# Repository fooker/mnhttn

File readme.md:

# mnhTTn

mnhTTn is a 36 key column-staggered split keyboard using Cherry MX ULP switches.
Designed to be as flat and lightweight as possible.

## Features
* [Cherry MX ULP Switches](https://www.cherry.de/mx-ulp-click)
* Bluetooth [via SEEED XIAO BLE](https://www.seeedstudio.com/Seeed-XIAO-BLE-nRF52840-p-5201.html)
* Only 7.2mm height

## Layout

## PCB
[Here](/board/) you can find the KiCad fies for the PCB.

To archive minimal height, you can order the PCB as low as 0.6mm thick.
But this requires additional attention while soldering on the swithches to prevent the board from warping caused by thermal expansion.

## Keycaps
There are no keycaps available off the shelve but have been manifactured using MJF in nylon.
The models are availabe [here](/keycaps/).

## Case
The (slightly overengineered) 3d printed case is available [here](/case/).
The case is best printed in PETG and you need the following material to build it:
- 2 round magnets with a diameter of 5mm and a height of 3mm
- 7 machines screws with a flat and countersunk head of size 2x10mm
- A festival/concert/entrance wristband of you'r favorite band or message
- A few drops of superglue

## Build Guide
The build guide can be found [here](/docs/buildguide.md).

## Firmware
My [ZMK config](https://github.com/fooker/mnhttn-zmk) for the mnhTTn.

## Photos
\
\
\
\

## Other Versions
There are other versions, derivats and spin-offs of this keyboard:
- **[mnhTTn48](https://github.com/venc0r/mnhttn)**: A 5*4+3+1 Keys versions with an additional top row and and extra key right above the diode array

If you have build or want to build something based on the mnhTTn keyboard or know about somebody that has created something with it, feel free to reach out and I will happly extend this list and provide support.

## Credits and inspirationt
The idea to creat such a keyboard emerged from the wonderfull [Click! Clack! Hack!](https://www.clickclackhack.de/) community.

The layout of the board is inspired by [TOTEM](https://github.com/GEIGEIGEIST/TOTEM).

And I got a lot of help and feedback from all around the mechanical keyboard community :heart:.

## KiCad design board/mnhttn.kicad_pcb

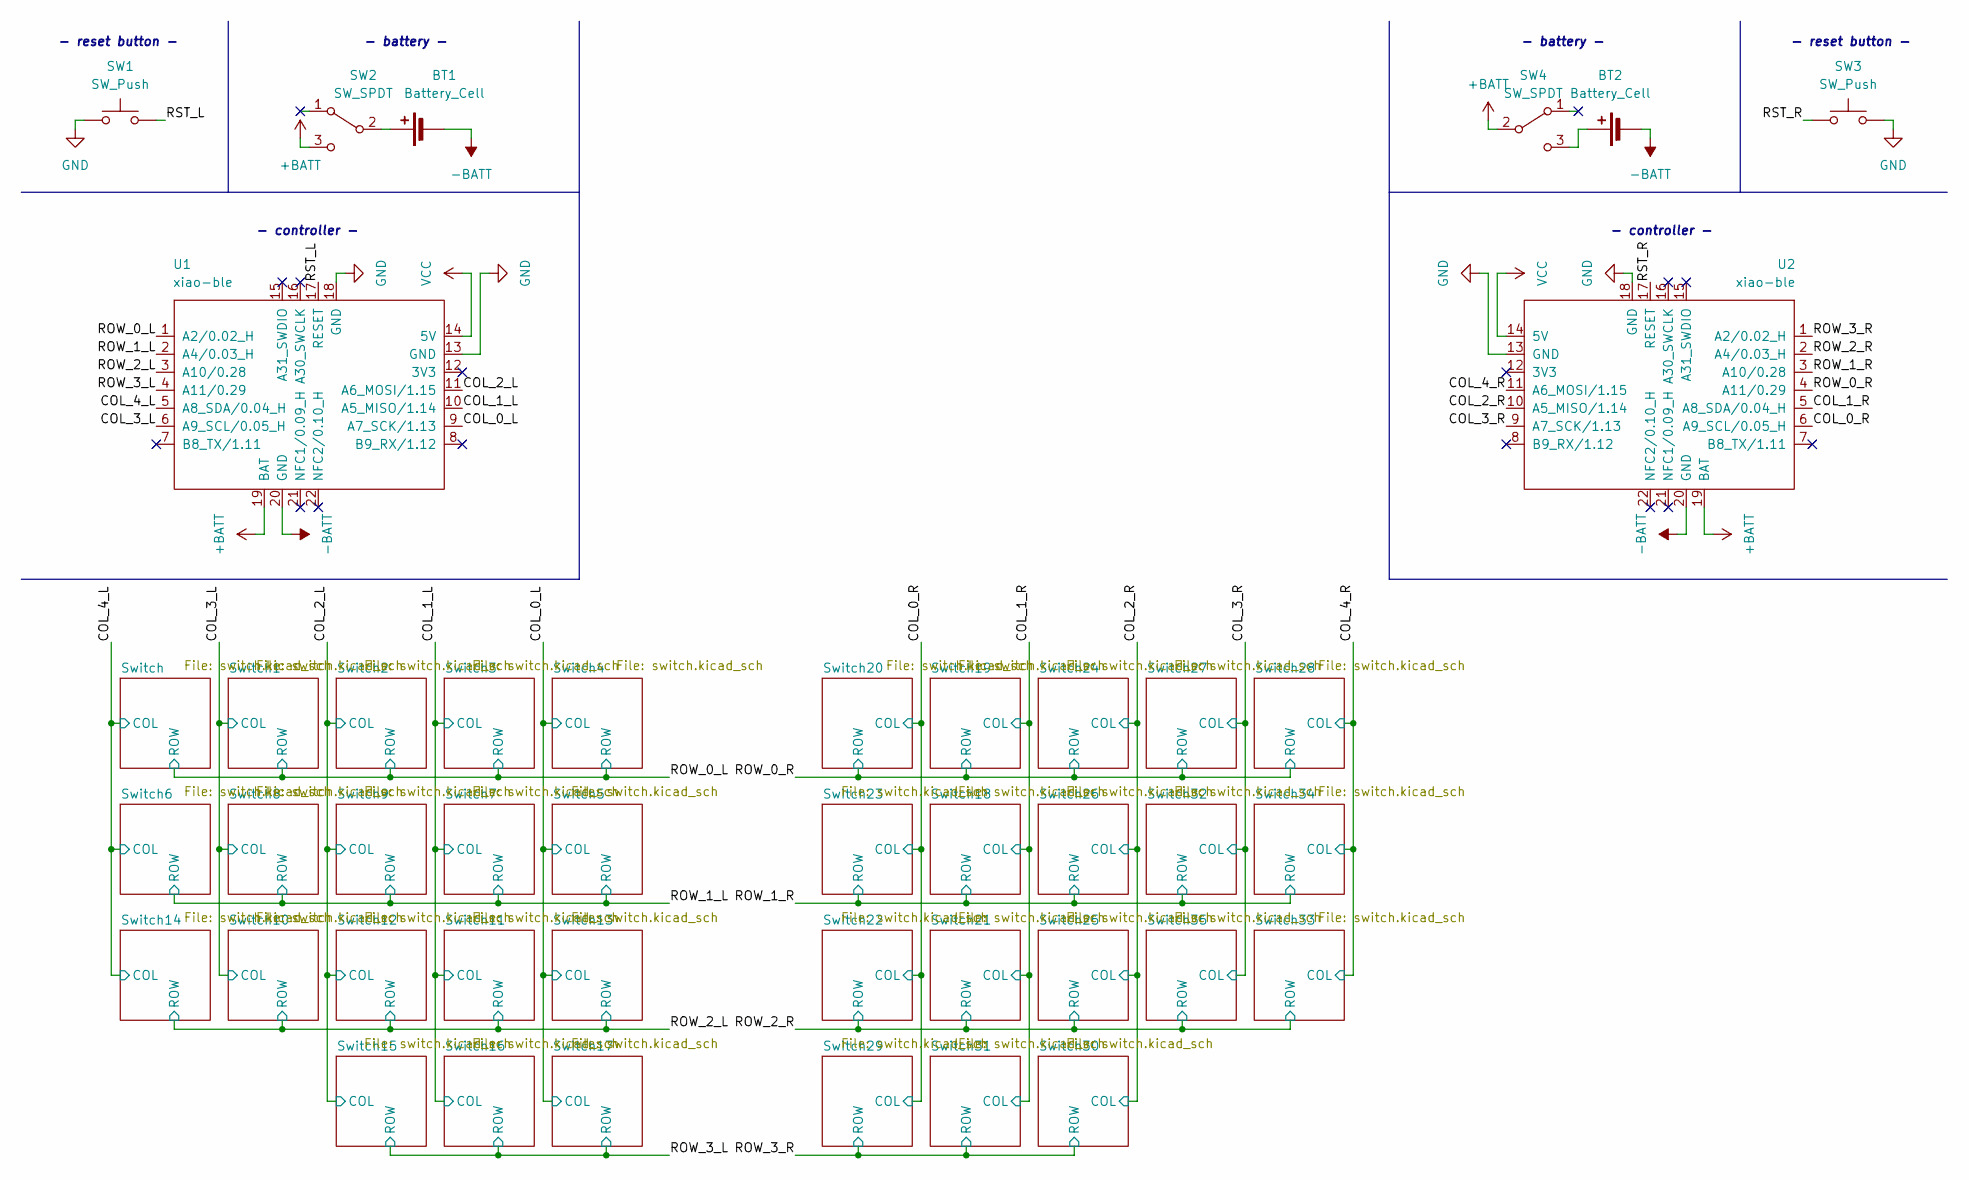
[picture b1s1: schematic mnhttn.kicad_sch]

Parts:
BT1, BT2: Battery_Cell; WAGO_2060-452_998-404; Digikey 2946-2060-472/998-404TR-ND
SW1, SW3: SW_Push; PushSwitch; Digikey EG5470TR-ND
SW2, SW4: SW_SPDT; MSK12C02; Digikey 732-13665-2-ND
U1, U2: xiao-ble; xiao-ble-smd; Digikey 1597-102010448-ND

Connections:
+BATT: SW2.3 (C), SW4.2 (B), U1.19 (BAT), U2.19 (BAT)
-BATT: BT1.2 (-), BT2.2 (-), U1.20 (GND), U2.20 (GND)
/COL_0_L: U1.9 (A7_SCK/1.13); also elsewhere on the board
/COL_0_R: U2.6 (A9_SCL/0.05_H); also elsewhere on the board
/COL_1_L: U1.10 (A5_MISO/1.14); also elsewhere on the board
/COL_1_R: U2.5 (A8_SDA/0.04_H); also elsewhere on the board
/COL_2_L: U1.11 (A6_MOSI/1.15); also elsewhere on the board
/COL_2_R: U2.10 (A5_MISO/1.14); also elsewhere on the board
/COL_3_L: U1.6 (A9_SCL/0.05_H); also elsewhere on the board
/COL_3_R: U2.9 (A7_SCK/1.13); also elsewhere on the board
/COL_4_L: U1.5 (A8_SDA/0.04_H); also elsewhere on the board
/COL_4_R: U2.11 (A6_MOSI/1.15); also elsewhere on the board
/ROW_0_L: U1.1 (A2/0.02_H); also elsewhere on the board
/ROW_0_R: U2.4 (A11/0.29); also elsewhere on the board
/ROW_1_L: U1.2 (A4/0.03_H); also elsewhere on the board
/ROW_1_R: U2.3 (A10/0.28); also elsewhere on the board
/ROW_2_L: U1.3 (A10/0.28); also elsewhere on the board
/ROW_2_R: U2.2 (A4/0.03_H); also elsewhere on the board
/ROW_3_L: U1.4 (A11/0.29); also elsewhere on the board
/ROW_3_R: U2.1 (A2/0.02_H); also elsewhere on the board
/RST_L: SW1.2, U1.17 (RESET)
/RST_R: SW3.2, U2.17 (RESET)
GND: SW1.1, SW3.1, U1.13 (GND), U1.18 (GND), U2.13 (GND), U2.18 (GND)
unnamed: BT1.1 (+), SW2.2 (B)
unnamed: BT2.1 (+), SW4.3 (C)
VCC: U1.14 (5V), U2.14 (5V)

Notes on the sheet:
- battery -
- reset button -
- controller -

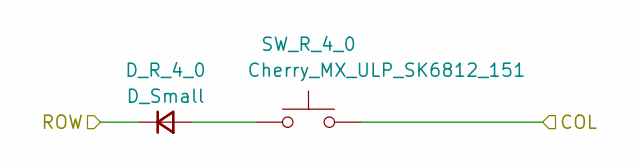
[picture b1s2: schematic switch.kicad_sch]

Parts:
D_R_4_0: D_Small; Diode_SOD123; Digikey 1655-1N4148WTR-ND
SW_R_4_0: Cherry_MX_ULP_SK6812_151; Cherry_MX_ULP; Digikey MX6C-K3NB

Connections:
/COL_4_R: SW_R_4_0.2; also elsewhere on the board
/ROW_0_R: D_R_4_0.1 (K); also elsewhere on the board
unnamed: D_R_4_0.2 (A), SW_R_4_0.1

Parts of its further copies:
D_L_0_0, D_L_0_1, D_L_0_2, D_L_0_3, D_L_1_0, D_L_1_1, D_L_1_2, D_L_1_3, D_L_2_0, D_L_2_1, D_L_2_2, D_L_2_3, D_L_3_0, D_L_3_1, D_L_3_2, D_L_4_0, D_L_4_1, D_L_4_2: D_Small; Diode_SOD123; Digikey 1655-1N4148WTR-ND
D_R_0_0, D_R_0_1, D_R_0_2, D_R_0_3, D_R_1_0, D_R_1_1, D_R_1_2, D_R_1_3, D_R_2_0, D_R_2_1, D_R_2_2, D_R_2_3, D_R_3_0, D_R_3_1, D_R_3_2, D_R_4_1, D_R_4_2: D_Small; Diode_SOD123; Digikey 1655-1N4148WTR-ND
SW_L_0_0, SW_L_0_1, SW_L_0_2, SW_L_0_3, SW_L_1_0, SW_L_1_1, SW_L_1_2, SW_L_1_3, SW_L_2_0, SW_L_2_1, SW_L_2_2, SW_L_2_3, SW_L_3_0, SW_L_3_1, SW_L_3_2, SW_L_4_0, SW_L_4_1, SW_L_4_2: Cherry_MX_ULP_SK6812_151; Cherry_MX_ULP; Digikey MX6C-K3NB
SW_R_0_0, SW_R_0_1, SW_R_0_2, SW_R_0_3, SW_R_1_0, SW_R_1_1, SW_R_1_2, SW_R_1_3, SW_R_2_0, SW_R_2_1, SW_R_2_2, SW_R_2_3, SW_R_3_0, SW_R_3_1, SW_R_3_2, SW_R_4_1, SW_R_4_2: Cherry_MX_ULP_SK6812_151; Cherry_MX_ULP; Digikey MX6C-K3NB

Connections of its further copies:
/COL_0_L: SW_L_0_0.2, SW_L_0_1.2, SW_L_0_2.2, SW_L_0_3.2; also elsewhere on the board
/COL_0_R: SW_R_0_0.2, SW_R_0_1.2, SW_R_0_2.2, SW_R_0_3.2; also elsewhere on the board
/COL_1_L: SW_L_1_0.2, SW_L_1_1.2, SW_L_1_2.2, SW_L_1_3.2; also elsewhere on the board
/COL_1_R: SW_R_1_0.2, SW_R_1_1.2, SW_R_1_2.2, SW_R_1_3.2; also elsewhere on the board
/COL_2_L: SW_L_2_0.2, SW_L_2_1.2, SW_L_2_2.2, SW_L_2_3.2; also elsewhere on the board
/COL_2_R: SW_R_2_0.2, SW_R_2_1.2, SW_R_2_2.2, SW_R_2_3.2; also elsewhere on the board
/COL_3_L: SW_L_3_0.2, SW_L_3_1.2, SW_L_3_2.2; also elsewhere on the board
/COL_3_R: SW_R_3_0.2, SW_R_3_1.2, SW_R_3_2.2; also elsewhere on the board
/COL_4_L: SW_L_4_0.2, SW_L_4_1.2, SW_L_4_2.2; also elsewhere on the board
/COL_4_R: SW_R_4_1.2, SW_R_4_2.2; also elsewhere on the board
/ROW_0_L: D_L_0_0.1 (K), D_L_1_0.1 (K), D_L_2_0.1 (K), D_L_3_0.1 (K), D_L_4_0.1 (K); also elsewhere on the board
/ROW_0_R: D_R_0_0.1 (K), D_R_1_0.1 (K), D_R_2_0.1 (K), D_R_3_0.1 (K); also elsewhere on the board
/ROW_1_L: D_L_0_1.1 (K), D_L_1_1.1 (K), D_L_2_1.1 (K), D_L_3_1.1 (K), D_L_4_1.1 (K); also elsewhere on the board
/ROW_1_R: D_R_0_1.1 (K), D_R_1_1.1 (K), D_R_2_1.1 (K), D_R_3_1.1 (K), D_R_4_1.1 (K); also elsewhere on the board
/ROW_2_L: D_L_0_2.1 (K), D_L_1_2.1 (K), D_L_2_2.1 (K), D_L_3_2.1 (K), D_L_4_2.1 (K); also elsewhere on the board
/ROW_2_R: D_R_0_2.1 (K), D_R_1_2.1 (K), D_R_2_2.1 (K), D_R_3_2.1 (K), D_R_4_2.1 (K); also elsewhere on the board
/ROW_3_L: D_L_0_3.1 (K), D_L_1_3.1 (K), D_L_2_3.1 (K); also elsewhere on the board
/ROW_3_R: D_R_0_3.1 (K), D_R_1_3.1 (K), D_R_2_3.1 (K); also elsewhere on the board
unnamed: D_L_0_0.2 (A), SW_L_0_0.1
unnamed: D_L_0_1.2 (A), SW_L_0_1.1
unnamed: D_L_0_2.2 (A), SW_L_0_2.1
unnamed: D_L_0_3.2 (A), SW_L_0_3.1
unnamed: D_L_1_0.2 (A), SW_L_1_0.1
unnamed: D_L_1_1.2 (A), SW_L_1_1.1
unnamed: D_L_1_2.2 (A), SW_L_1_2.1
unnamed: D_L_1_3.2 (A), SW_L_1_3.1
unnamed: D_L_2_0.2 (A), SW_L_2_0.1
unnamed: D_L_2_1.2 (A), SW_L_2_1.1
unnamed: D_L_2_2.2 (A), SW_L_2_2.1
unnamed: D_L_2_3.2 (A), SW_L_2_3.1
unnamed: D_L_3_0.2 (A), SW_L_3_0.1
unnamed: D_L_3_1.2 (A), SW_L_3_1.1
unnamed: D_L_3_2.2 (A), SW_L_3_2.1
unnamed: D_L_4_0.2 (A), SW_L_4_0.1
unnamed: D_L_4_1.2 (A), SW_L_4_1.1
unnamed: D_L_4_2.2 (A), SW_L_4_2.1
unnamed: D_R_0_0.2 (A), SW_R_0_0.1
unnamed: D_R_0_1.2 (A), SW_R_0_1.1
unnamed: D_R_0_2.2 (A), SW_R_0_2.1
unnamed: D_R_0_3.2 (A), SW_R_0_3.1
unnamed: D_R_1_0.2 (A), SW_R_1_0.1
unnamed: D_R_1_1.2 (A), SW_R_1_1.1
unnamed: D_R_1_2.2 (A), SW_R_1_2.1
unnamed: D_R_1_3.2 (A), SW_R_1_3.1
unnamed: D_R_2_0.2 (A), SW_R_2_0.1
unnamed: D_R_2_1.2 (A), SW_R_2_1.1
unnamed: D_R_2_2.2 (A), SW_R_2_2.1
unnamed: D_R_2_3.2 (A), SW_R_2_3.1
unnamed: D_R_3_0.2 (A), SW_R_3_0.1
unnamed: D_R_3_1.2 (A), SW_R_3_1.1
unnamed: D_R_3_2.2 (A), SW_R_3_2.1
unnamed: D_R_4_1.2 (A), SW_R_4_1.1
unnamed: D_R_4_2.2 (A), SW_R_4_2.1

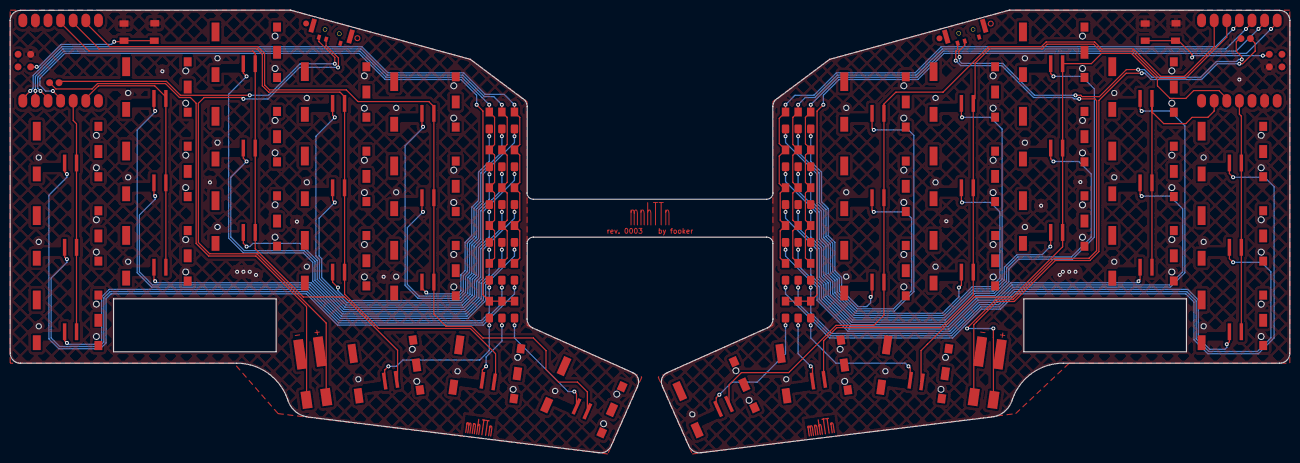
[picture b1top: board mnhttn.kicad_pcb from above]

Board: 2 copper layers, 257.3 x 88.6 mm, 80 parts (0 on the bottom side), 62 nets.

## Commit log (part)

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2023-05-09 Initial
2023-05-17 Initial firmware
2023-05-17 Fix PCB problems
2023-12-26 firmware: layout
2023-12-26 firmware: to seperate repo
2024-02-15 docs
2024-02-15 connect pin pairs on switch
2024-02-15 build guide
2024-02-15 fixed typo
2024-02-20 Add makefile for board
2024-05-29 Improved project layout
2024-06-30 Create LICENSE
2024-08-01 Switch ampersand and percent
2024-08-01 Add derived work to readme
2025-01-08 Replace umlauts to match workman
2025-01-26 Add switch alignment bores
2025-01-26 Fix PCB bundle building
2025-02-28 kicad update
2025-03-01 Switched to SMD switches
2025-11-11 Add battery connector
2026-05-15 SMD only, On/Off symbole, Cleanup
